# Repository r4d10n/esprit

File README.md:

# ESPRIT
ESP Radio Interface - Through Hole version with ESP32 DOIT devboard (based on [ESPRI](https://github.com/kamilsss655/ESPRI) project)

ESPRI project provides an integrated Digital Audio / Programming Interface for Quangsheng UV-K5, Baofeng UV-5R and other Kenwood-style connector radios, similar to the excellent [AIOC](https://github.com/skuep/AIOC) project. With ESP32 offering WiFi/Bluetooth connectivity,  the possibilities are endless !

Since Lolin32 Lite is not common in this part of the world and SMD sourcing / assembly is still cumbersome, we've attempted a Through Hole version for the most common 30 pin [ESP32 DOIT board](https://mischianti.org/doit-esp32-dev-kit-v1-high-resolution-pinout-and-specs/).

Changes:

- Since there are a lot of unpopulated I/Os, we've added 0.91" OLED, couple of LEDs, Switches and one more Touchpad Button. 
- The ADC/DAC IO pins have been broken out to a header
- Header Pins for Radio PWR, 5v and 3.3v 
- SMD 2N7002 has been replaced with THT 2N7000  

[[Interactive BOM]](https://htmlpreview.github.io/?https://github.com/r4d10n/esprit/blob/main/ibom/ibom.html) - [[Schematics]](https://kicanvas.org/?github=https://github.com/r4d10n/esprit/blob/main/espri-doit.kicad_sch) - [[PCB]](https://kicanvas.org/?github=https://github.com/r4d10n/esprit/blob/main/espri-doit.kicad_pcb) - [[Gerbers]](https://github.com/r4d10n/esprit/blob/main/production/espri-doit.zip)

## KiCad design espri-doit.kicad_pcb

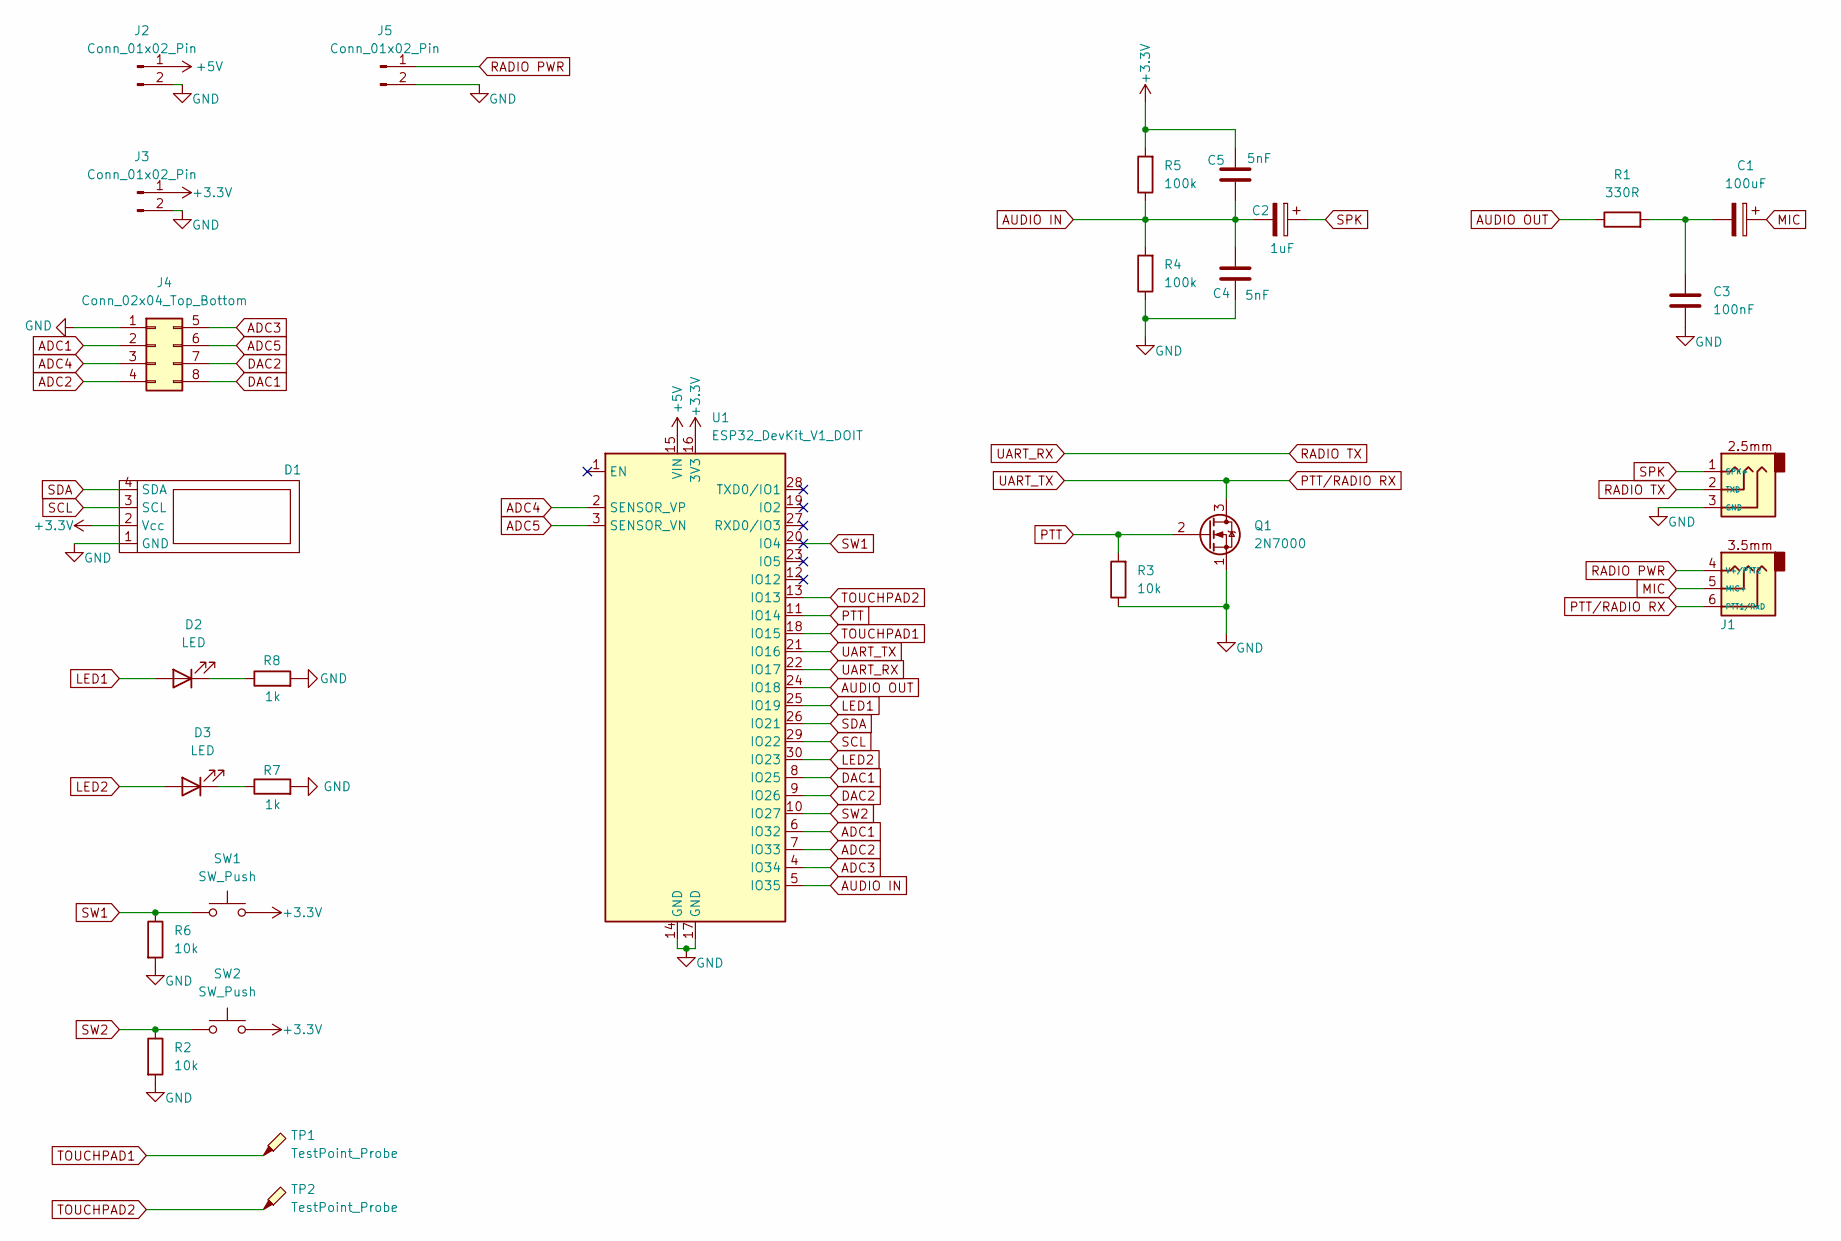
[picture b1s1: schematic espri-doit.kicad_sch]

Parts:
C1: 100uF; CP_Radial_D4.0mm_P2.00mm
C2: 1uF; CP_Radial_D4.0mm_P2.00mm
C3: 100nF; C_Rect_L4.0mm_W2.5mm_P2.50mm
C4, C5: 5nF; C_Rect_L4.0mm_W2.5mm_P2.50mm
D1: OLED 0.91 128x38
D2, D3: LED; LED_D3.0mm
J1: Rig Audio Connector
J2, J3, J5: Conn_01x02_Pin; PinSocket_1x02_P2.54mm_Vertical
J4: Conn_02x04_Top_Bottom; PinHeader_2x04_P2.54mm_Vertical
Q1: 2N7000; TO-92_Inline
R1: 330R; R_Axial_DIN0309_L9.0mm_D3.2mm_P12.70mm_Horizontal
R2, R3, R6: 10k; R_Axial_DIN0309_L9.0mm_D3.2mm_P12.70mm_Horizontal
R4, R5: 100k; R_Axial_DIN0309_L9.0mm_D3.2mm_P12.70mm_Horizontal
R7, R8: 1k; R_Axial_DIN0309_L9.0mm_D3.2mm_P12.70mm_Horizontal
SW1, SW2: SW_Push; SW_PUSH_6mm_H4.3mm
TP1, TP2: TestPoint_Probe; TestPoint_Pad_4.0x4.0mm
U1: ESP32_DevKit_V1_DOIT; esp32 devkit doit

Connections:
+3.3V: C5.1, D1.2 (Vcc), J3.1, R5.2, SW1.2, SW2.2, U1.16 (3V3)
+5V: J2.1, U1.15 (VIN)
ADC1: J4.2, U1.6 (IO32)
ADC2: J4.4, U1.7 (IO33)
ADC3: J4.5, U1.4 (IO34)
ADC4: J4.3, U1.2 (SENSOR_VP)
ADC5: J4.6, U1.3 (SENSOR_VN)
AUDIO IN: C2.2, C4.1, C5.2, R4.2, R5.1, U1.5 (IO35)
AUDIO OUT: R1.1, U1.24 (IO18)
DAC1: J4.8, U1.8 (IO25)
DAC2: J4.7, U1.9 (IO26)
GND: C3.2, C4.2, D1.1 (GND), J1.3 (GND), J2.2, J3.2, J4.1, J5.2, Q1.1 (S), R2.2, R3.1, R4.1, R6.2, R7.2, R8.2, U1.14 (GND), U1.17 (GND)
LED1: D2.2 (A), U1.25 (IO19)
LED2: D3.2 (A), U1.30 (IO23)
MIC: C1.1, J1.5 (MIC+)
unnamed: C1.2, C3.1, R1.2
unnamed: D2.1 (K), R8.1
unnamed: D3.1 (K), R7.1
PTT: Q1.2 (G), R3.2, U1.11 (IO14)
PTT/RADIO RX: J1.6 (PTT1/RxD), Q1.3 (D), U1.21 (IO16)
RADIO PWR: J1.4 (V+/PTT2), J5.1
RADIO TX: J1.2 (TXD), U1.22 (IO17)
SCL: D1.3 (SCL), U1.29 (IO22)
SDA: D1.4 (SDA), U1.26 (IO21)
SPK: C2.1, J1.1 (SPK+)
SW1: R6.1, SW1.1, U1.20 (IO4)
SW2: R2.1, SW2.1, U1.10 (IO27)
TOUCHPAD1: TP1.1, U1.18 (IO15)
TOUCHPAD2: TP2.1, U1.13 (IO13)

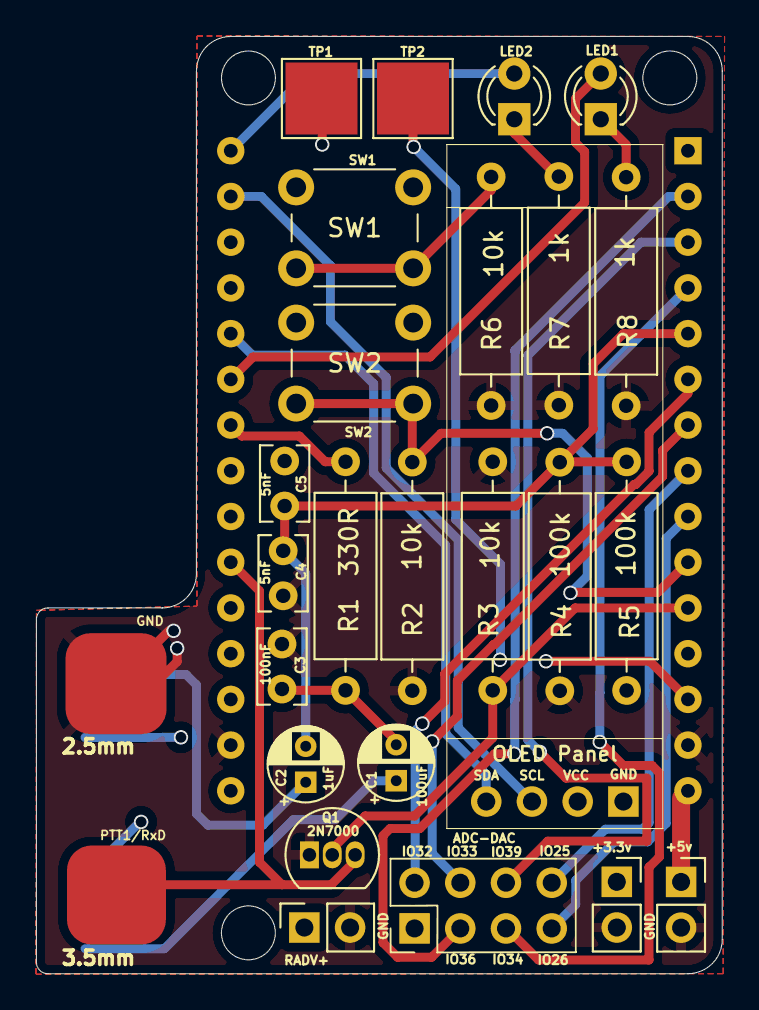
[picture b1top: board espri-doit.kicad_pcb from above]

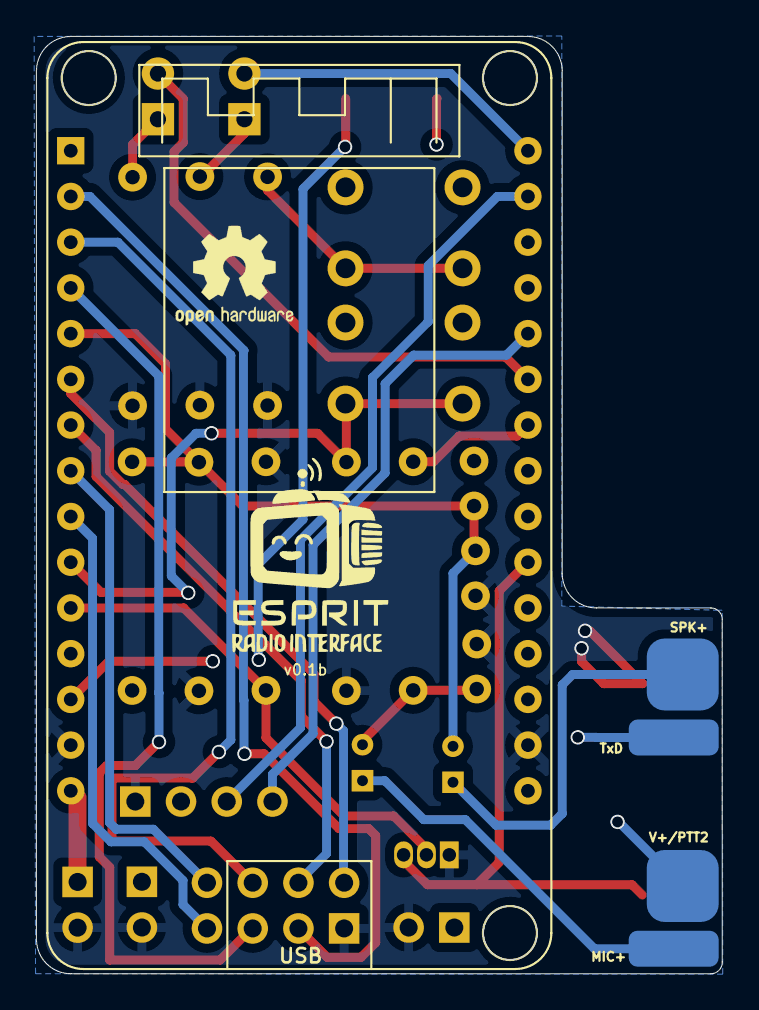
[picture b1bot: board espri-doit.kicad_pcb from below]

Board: 4 copper layers, 38.1 x 52.1 mm, 27 parts (3 on the bottom side), 29 nets.

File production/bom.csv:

Designator,Footprint,Quantity,Value,LCSC Part #
C1,CP_Radial_D4.0mm_P2.00mm,1,100uF,
C2,CP_Radial_D4.0mm_P2.00mm,1,1uF,
C3,C_Rect_L4.0mm_W2.5mm_P2.50mm,1,100nF,
"C4, C5",C_Rect_L4.0mm_W2.5mm_P2.50mm,2,5nF,
D1,OLED 0.91 128x38,1,~,
"D2, D3",LED_D3.0mm,2,LED,
J1,Rig Audio Connector,1,~,
"J2, J3, J5",PinSocket_1x02_P2.54mm_Vertical,3,Conn_01x02_Pin,
J4,PinSocket_2x04_P2.54mm_Vertical,1,Conn_02x04_Top_Bottom,
Q1,TO-92_Inline,1,2N7000,
R1,R_Axial_DIN0309_L9.0mm_D3.2mm_P12.70mm_Horizontal,1,330R,
"R2, R3, R6",R_Axial_DIN0309_L9.0mm_D3.2mm_P12.70mm_Horizontal,3,10k,
"R4, R5",R_Axial_DIN0309_L9.0mm_D3.2mm_P12.70mm_Horizontal,2,100k,
"R7, R8",R_Axial_DIN0309_L9.0mm_D3.2mm_P12.70mm_Horizontal,2,1k,
"SW1, SW2",SW_PUSH_6mm_H4.3mm,2,SW_Push,
"TP1, TP2",TestPoint_Pad_4.0x4.0mm,2,TestPoint_Probe,
U1,esp32 devkit doit,1,ESP32_DevKit_V1_DOIT,

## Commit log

2024-05-10 Add render
